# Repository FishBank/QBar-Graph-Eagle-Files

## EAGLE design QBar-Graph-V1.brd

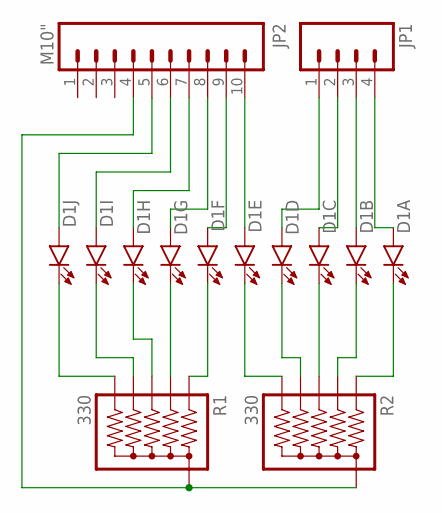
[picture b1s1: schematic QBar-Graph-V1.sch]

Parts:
D1: LED_BARGRAPH_10; LED_BARGAPH_10
JP1: M04PTH; 1X04
JP2: M10"; 1X10
R1, R2: 330; RPACK-SIP-PTH-5

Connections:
unnamed: D1.11 (C), R1.P$6 (6)
unnamed: D1.12 (C), R1.P$5 (5)
unnamed: D1.13 (C), R1.P$4 (4)
unnamed: D1.14 (C), R1.P$3 (3)
unnamed: D1.15 (C), R1.P$2 (2)
unnamed: D1.20 (C), R2.P$2 (2)
unnamed: D1.19 (C), R2.P$3 (3)
unnamed: D1.18 (C), R2.P$4 (4)
unnamed: D1.17 (C), R2.P$5 (5)
unnamed: D1.16 (C), R2.P$6 (6)
unnamed: JP2.4, R1.P$1 (1), R2.P$1 (1)
unnamed: D1.1 (A), JP1.4
unnamed: D1.2 (A), JP1.3
unnamed: D1.3 (A), JP1.2
unnamed: D1.4 (A), JP1.1
unnamed: D1.5 (A), JP2.10
unnamed: D1.6 (A), JP2.9
unnamed: D1.7 (A), JP2.8
unnamed: D1.8 (A), JP2.7
unnamed: D1.9 (A), JP2.6
unnamed: D1.10 (A), JP2.5

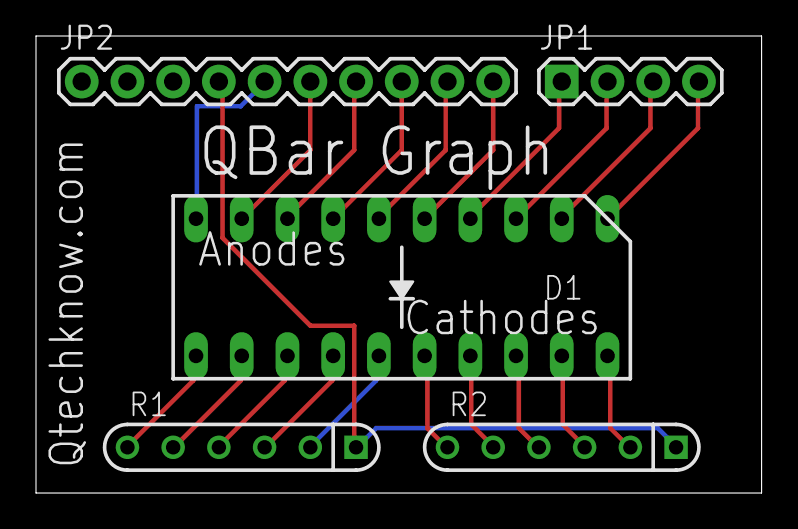
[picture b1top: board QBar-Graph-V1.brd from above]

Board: 2 copper layers, 40.3 x 25.4 mm, 5 parts (0 on the bottom side), 21 nets.

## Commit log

2012-07-13 Schematic

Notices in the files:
parts and their libraries:
SFE Passives: Licensing: CC v3.0 Share-Alike You are welcome to use this library for commercial purposes.
